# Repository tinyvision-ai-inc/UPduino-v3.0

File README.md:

# UPduino-v3.0 and 3.1

Image credit: Gregory Benjamin

## UPDuino v3.1: PCB Design Files, Designs, Documentation

The UPDuino v3.1 is a small, low cost FPGA board. The board features an on-board FPGA programmer, flash and LED with _all_ FPGA pins brought out to easy to use 0.1" header pins for fast prototyping.

The tinyVision.ai UPduino v3.x Board Features:

* Lattice UltraPlus ICE40UP5K FPGA with 5.3K LUTs, 1Mb SPRAM, 120Kb DPRAM, 8 Multipliers
* FTDI FT232H USB to SPI Device
* _ALL_ 32 FPGA GPIO on 0.1” headers
* 4MB SPI Flash
* RGB LED
* On board 3.3V and 1.2V Regulators, can supply 3.3V to your project
* Open source schematic and layout using KiCAD design tools
* Integrated into the open source [APIO toolchain](https://github.com/FPGAwars/apio)
* Works with [IceStudio](https://github.com/FPGAwars/icestudio)<sup>[nightly/dev branch only at the moment](https://downloads.icestudio.io/)</sup>

Please see the [wiki page](https://github.com/tinyvision-ai-inc/UPduino-v3.0/wiki) for the changes that were implemented from v2.1. Some salient features are:
* 4 layer board with a solid ground plane, proper layout/decoupling for good signal integrity and FPGA operation
* Access to on-board 12MHz oscillator using a jumper
* _All_ FPGA pins including LED driver pins are brought to 0.1" headers
* qSPI Flash capable
* tinyFPGA bootloader compatible 

Here are some resources for you:
* [Documentation](https://upduino.readthedocs.io/) (beyond what's on this GitHub)
* [Discord channel](https://discord.gg/3qbXujE)
* [Schematic](./Board/v3.0/UPduino_v3.0.pdf)
* [AssemblyDrawing](./Board/v3.0/UPduino_v3.0Assembly.html)
* [Blinking LED](./RTL/blink_led)
 
TinyVision.ai blog posts:
* [Magic Smoke and PTC's](https://blogs.tinyvision.ai/upduino/power/ptc/2021/12/31/magic-smoke-and-PTCs.html)
* [Lattice Modelsim on Windows](https://blogs.tinyvision.ai/modelsim/windows/linux/radiant/lattice/2022/01/01/Using-Lattice-Modelsim-on-Win-Linux.html)
* [Ground trampolines and Phase Locked Loops](https://tinyvision.ai/blogs/processing-at-the-edge/ground-trampolines-and-phase-locked-loops)

You can buy this board here:
US and non-EU orders: . 

EU Orders with VAT paid: 

For expedited shipping options, please visit the storefront at www.tinyvision.ai or email us directly at: sales at tinyvision dot ai.

## Useful links
* [Digi-Key Intro to FPGA Video series](https://youtube.com/playlist?list=PLEBQazB0HUyT1WmMONxRZn9NmQ_9CIKhb)
* [osresearch](https://github.com/osresearch/up5k): large collection of very useful code and a good overview.
* [UPduino FPGA tutorial using APIO](https://blog.idorobots.org/entries/upduino-fpga-tutorial.html)
* [A very detailed blog on implementing a RISCV in the FPGA](https://pingu98.wordpress.com/2019/04/08/)
* [Lattice iCECube2 tutorial](https://hsel.co.uk/2018/05/21/lattice-ice40-ultra-plus-fpga-gnarly-grey-upduino-tutorial-1-the-basics/)
* [Open FPGA verilog Tutorial](https://github.com/Obijuan/open-fpga-verilog-tutorial/wiki)

## The next generation of Upduino (coming soon)
* [pico-ice](https://github.com/tinyvision-ai-inc/pico-ice)

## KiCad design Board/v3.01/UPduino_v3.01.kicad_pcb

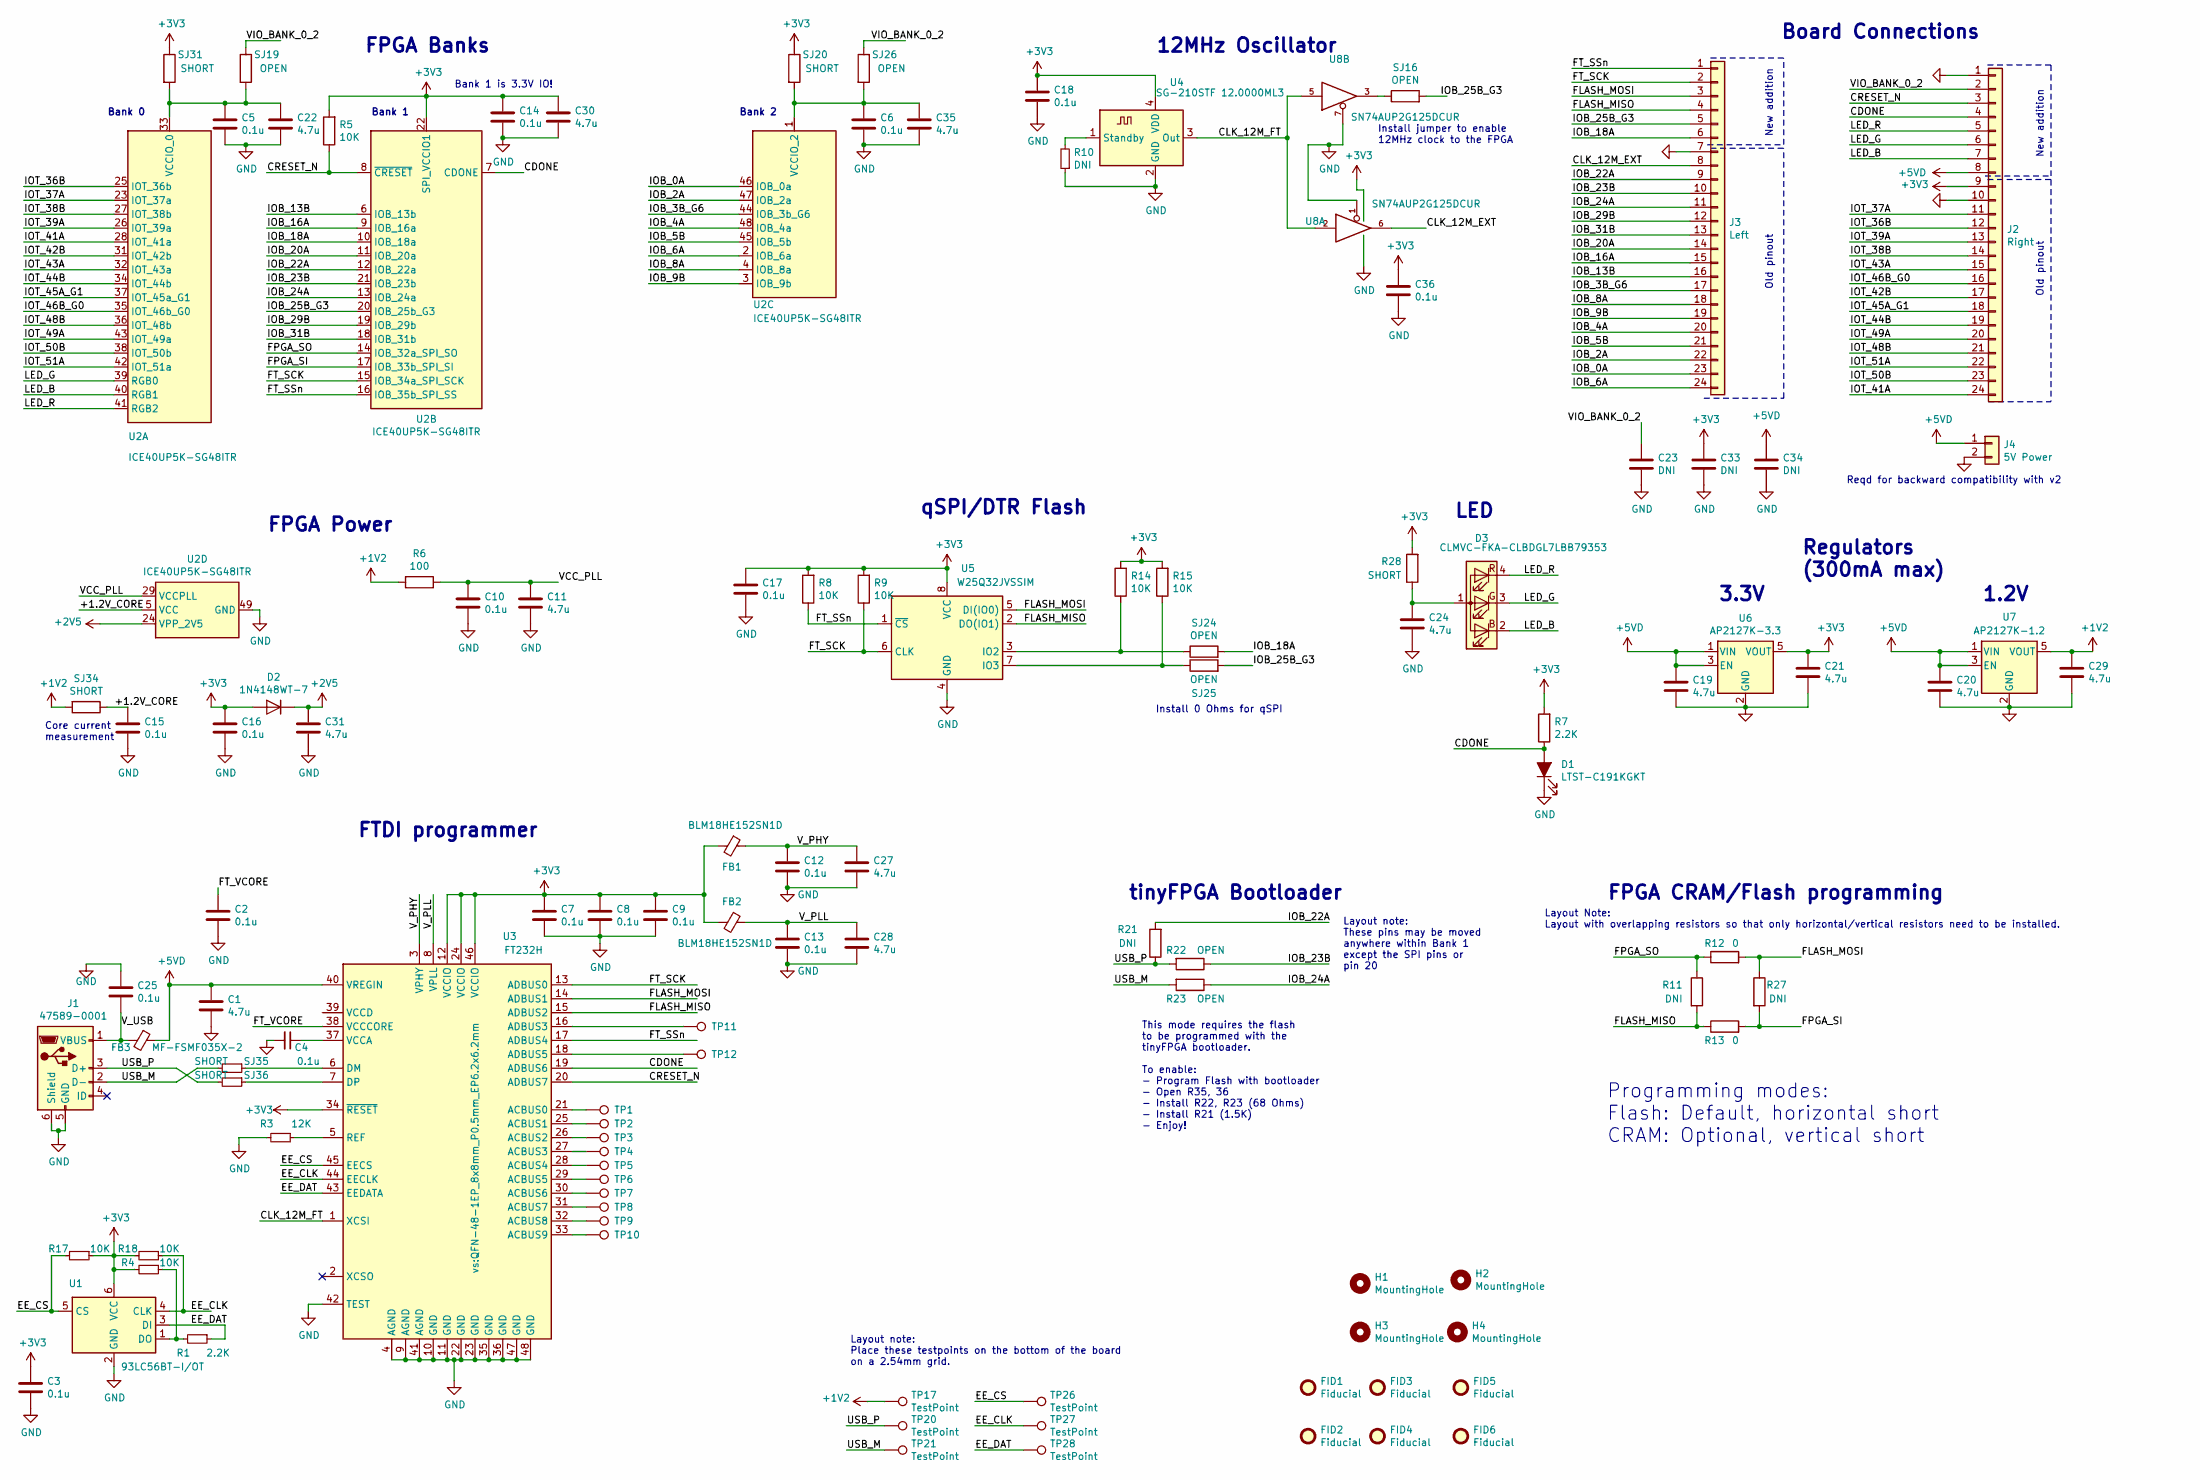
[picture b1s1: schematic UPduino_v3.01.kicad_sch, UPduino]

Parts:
C1, C11, C19, C20, C21, C22, C24, C27, C28, C29, C30, C31, C35: 4.7u; C_0603_1608Metric
C2, C3, C4, C6, C7, C8, C9, C10, C12, C13, C14, C15, C16, C17, C18, C25, C36: 0.1u; C_0603_1608Metric
C5: 0.1u; C_0603_1608Metric; MPN C1005X5R0J104K050BA
C23, C33, C34: DNI; C_0603_1608Metric
D1: LTST-C191KGKT; LED_0603_1608Metric
D2: 1N4148WT-7; D_SOD-523
D3: CLMVC-FKA-CLBDGL7LBB79353; LED_Cree-PLCC4_2x2mm_CW
FB1, FB2: BLM18HE152SN1D; L_0603_1608Metric
FB3: MF-FSMF035X-2; L_0603_1608Metric
FID1, FID2, FID3, FID4, FID5, FID6: Fiducial; Fiducial_0.75mm_Mask1.5mm
H1, H2, H3, H4: MountingHole; MountingHole_2.5mm_M3
J1: 47589-0001; USB_Micro_AB_Female_0475890001
J2: Right; PinHeader_1x24_P2.54mm_Vertical
J3: Left; PinHeader_1x24_P2.54mm_Vertical
J4: 5V Power; PinHeader_1x02_P2.54mm_Vertical
R1, R7: 2.2K; R_0603_1608Metric
R3: 12K; R_0603_1608Metric
R4, R5, R8, R9, R14, R15, R17, R18: 10K; R_0603_1608Metric
R6: 100; R_0603_1608Metric
R10, R11, R21, R27: DNI; R_0603_1608Metric
R12, R13: 0; R_0603_1608Metric
R22, R23: OPEN; SolderJumper-2_0603_Open_TrianglePad1.0x1.5mm
R28: SHORT; ShortedJumper-2_P1.3mm_Bridged_Pad1.0x1.0mm
SJ16, SJ19, SJ24, SJ25, SJ26: OPEN; SolderJumper-2_0603_Open_TrianglePad1.0x1.5mm
SJ20, SJ31, SJ34, SJ35, SJ36: SHORT; ShortedJumper-2_P1.3mm_Bridged_Pad1.0x1.0mm
TP1, TP2, TP3, TP4, TP5, TP6, TP7, TP8, TP9, TP10, TP11, TP12, TP17, TP20, TP21, TP26, TP27, TP28: TestPoint; TestPoint_Pad_D1.0mm
U1: 93LC56BT-I/OT; SOT-23-6
U2: ICE40UP5K-SG48ITR; QFN-48-1EP_7x7mm_P0.5mm_EP5.6x5.6mm
U3: FT232H; QFN-48-1EP_8x8mm_P0.5mm_EP6.2x6.2mm
U4: SG-210STF 12.0000ML3; Oscillator_SMD_Abracon_ASDMB-4Pin_2.5x2.0mm
U5: W25Q32JVSSIM; SOIC-8_5.23x5.23mm_P1.27mm
U6: AP2127K-3.3; SOT-23-5
U7: AP2127K-1.2; SOT-23-5
U8: SN74AUP2G125DCUR; VSSOP-8_2.3x2mm_P0.5mm

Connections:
+1V2: C29.1, R6.2, SJ34.2, TP17.1, U7.5 (VOUT)
+2V5: C31.1, D2.1 (K), U2.24 (VPP_2V5)
+3V3: C3.1, C7.1, C8.1, C9.1, C14.1, C16.1, C17.1, C18.1, C21.1, C30.1, C33.1, C36.1, D2.2 (A), FB1.2, FB2.2, J2.9, R4.2, R5.2, R7.2, R8.2, R9.2, R14.2, R15.2, R17.1, R18.2, R28.2, SJ20.1, SJ31.1, U1.6 (VCC), U2.22 (SPI_VCCIO1), U3.12 (VCCIO), U3.24 (VCCIO), U3.34 (~RESET), U3.46 (VCCIO), U4.4 (VDD), U5.8 (VCC), U6.5 (VOUT), U8.8 (VCC)
+5VD: C1.1, C19.1, C20.1, C34.1, FB3.1, J2.8, J4.1, U3.40 (VREGIN), U6.1 (VIN), U6.3 (EN), U7.1 (VIN), U7.3 (EN)
/+1.2V_CORE: C15.1, SJ34.1, U2.5 (VCC), U2.30 (VCC)
/CDONE: D1.2 (A), J2.4, R7.1, U2.7 (CDONE), U3.19 (ADBUS6)
/CLK_12M_EXT: J3.8, U8.6
/CLK_12M_FT: U3.1 (XCSI), U4.3 (Out), U8.2, U8.5
/CRESET_N: J2.3, R5.1, U2.8 (~CRESET), U3.20 (ADBUS7)
/EE_CLK: R18.1, TP27.1, U1.4 (CLK), U3.44 (EECLK)
/EE_CS: R17.2, TP26.1, U1.5 (CS), U3.45 (EECS)
/EE_DAT: R1.1, TP28.1, U1.3 (DI), U3.43 (EEDATA)
/FLASH_MISO: J3.4, R11.2, R13.1, U3.15 (ADBUS2), U5.2 (DO(IO1))
/FLASH_MOSI: J3.3, R12.2, R27.1, U3.14 (ADBUS1), U5.5 (DI(IO0))
/FPGA_SI: R13.2, R27.2, U2.17 (IOB_33b_SPI_SI)
/FPGA_SO: R11.1, R12.1, U2.14 (IOB_32a_SPI_SO)
/FT_SCK: J3.2, R9.1, U2.15 (IOB_34a_SPI_SCK), U3.13 (ADBUS0), U5.6 (CLK)
/FT_SSn: J3.1, R8.1, U2.16 (IOB_35b_SPI_SS), U3.17 (ADBUS4), U5.1 (~CS)
/FT_VCORE: C2.1, U3.38 (VCCCORE)
/IOB_0A: J3.23, U2.46 (IOB_0a)
/IOB_2A: J3.22, U2.47 (IOB_2a)
/IOB_3B_G6: J3.17, U2.44 (IOB_3b_G6)
/IOB_4A: J3.20, U2.48 (IOB_4a)
/IOB_5B: J3.21, U2.45 (IOB_5b)
/IOB_6A: J3.24, U2.2 (IOB_6a)
/IOB_8A: J3.18, U2.4 (IOB_8a)
/IOB_9B: J3.19, U2.3 (IOB_9b)
/IOB_13B: J3.16, U2.6 (IOB_13b)
/IOB_16A: J3.15, U2.9 (IOB_16a)
/IOB_18A: J3.6, SJ24.2, U2.10 (IOB_18a)
/IOB_20A: J3.14, U2.11 (IOB_20a)
/IOB_22A: J3.9, R21.2, U2.12 (IOB_22a)
/IOB_23B: J3.10, R22.1, U2.21 (IOB_23b)
/IOB_24A: J3.11, R23.1, U2.13 (IOB_24a)
/IOB_25B_G3: J3.5, SJ16.2, SJ25.2, U2.20 (IOB_25b_G3)
/IOB_29B: J3.12, U2.19 (IOB_29b)
/IOB_31B: J3.13, U2.18 (IOB_31b)
/IOT_36B: J2.12, U2.25 (IOT_36b)
/IOT_37A: J2.11, U2.23 (IOT_37a)
/IOT_38B: J2.14, U2.27 (IOT_38b)
/IOT_39A: J2.13, U2.26 (IOT_39a)
/IOT_41A: J2.24, U2.28 (IOT_41a)
/IOT_42B: J2.17, U2.31 (IOT_42b)
/IOT_43A: J2.15, U2.32 (IOT_43a)
/IOT_44B: J2.19, U2.34 (IOT_44b)
/IOT_45A_G1: J2.18, U2.37 (IOT_45a_G1)
/IOT_46B_G0: J2.16, U2.35 (IOT_46b_G0)
/IOT_48B: J2.21, U2.36 (IOT_48b)
/IOT_49A: J2.20, U2.43 (IOT_49a)
/IOT_50B: J2.23, U2.38 (IOT_50b)
/IOT_51A: J2.22, U2.42 (IOT_51a)
/LED_B: D3.2 (RK), J2.7, U2.40 (RGB1)
/LED_G: D3.3 (GK), J2.6, U2.39 (RGB0)
/LED_R: D3.4 (BK), J2.5, U2.41 (RGB2)
/USB_M: J1.2 (D-), R23.2, SJ35.2, TP21.1
/USB_P: J1.3 (D+), R21.1, R22.2, SJ36.2, TP20.1
/VCC_PLL: C10.1, C11.1, R6.1, U2.29 (VCCPLL)
/VIO_BANK_0_2: C23.1, J2.2, SJ19.1, SJ26.1
/V_PHY: C12.1, C27.1, FB1.1, U3.3 (VPHY)
/V_PLL: C13.1, C28.1, FB2.1, U3.8 (VPLL)
/V_USB: C25.2, FB3.2, J1.1 (VBUS)
GND: C1.2, C2.2, C3.2, C4.2, C5.2, C6.2, C7.2, C8.2, C9.2, C10.2, C11.2, C12.2, C13.2, C14.2, C15.2, C16.2, C17.2, C18.2, C19.2, C20.2, C21.2, C22.2, C23.2, C24.2, C25.1, C27.2, C28.2, C29.2, C30.2, C31.2, C33.2, C34.2, C35.2, C36.2, D1.1 (K), J1.5 (GND), J1.6 (Shield), J2.1, J2.10, J3.7, J4.2, R3.2, R10.1, U1.2 (GND), U2.49 (GND), U3.4 (AGND), U3.9 (AGND), U3.10 (GND), U3.11 (GND), U3.22 (GND), U3.23 (GND), U3.35 (GND), U3.36 (GND), U3.41 (AGND), U3.42 (TEST), U3.47 (GND), U3.48 (GND), U4.2 (GND), U5.4 (GND), U6.2 (GND), U7.2 (GND), U8.1, U8.4 (GND), U8.7
unnamed: C4.1, U3.37 (VCCA)
unnamed: C5.1, C22.1, SJ19.2, SJ31.2, U2.33 (VCCIO_0)
unnamed: C24.1, D3.1 (A), R28.1
unnamed: C6.1, C35.1, SJ20.2, SJ26.2, U2.1 (VCCIO_2)
unnamed: R1.2, R4.1, U1.1 (DO)
unnamed: R3.1, U3.5 (REF)
unnamed: R10.2, U4.1 (Standby)
unnamed: R14.1, SJ24.1, U5.3 (IO2)
unnamed: R15.1, SJ25.1, U5.7 (IO3)
unnamed: SJ16.1, U8.3
unnamed: SJ35.1, U3.6 (DM)
unnamed: SJ36.1, U3.7 (DP)
unnamed: TP1.1, U3.21 (ACBUS0)
unnamed: TP2.1, U3.25 (ACBUS1)
unnamed: TP3.1, U3.26 (ACBUS2)
unnamed: TP4.1, U3.27 (ACBUS3)
unnamed: TP5.1, U3.28 (ACBUS4)
unnamed: TP6.1, U3.29 (ACBUS5)
unnamed: TP7.1, U3.30 (ACBUS6)
unnamed: TP8.1, U3.31 (ACBUS7)
unnamed: TP9.1, U3.32 (ACBUS8)
unnamed: TP10.1, U3.33 (ACBUS9)
unnamed: TP11.1, U3.16 (ADBUS3)
unnamed: TP12.1, U3.18 (ADBUS5)

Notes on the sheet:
FPGA Banks
FPGA Power
Install jumper to enable 12MHz clock to the FPGA
Layout note: Place these testpoints on the bottom of the board on a 2.54mm grid.
New addition
Layout Note: Layout with overlapping resistors so that only horizontal/vertical resistors need to be installed.
Programming modes: Flash: Default, horizontal short CRAM: Optional, vertical short
Board Connections
Bank 2
Reqd for backward compatibility with v2
Old pinout
Layout note: These pins may be moved anywhere within Bank 1 except the SPI pins or pin 20
tinyFPGA Bootloader
Core current measurement
Install 0 Ohms for qSPI
1.2V
Bank 1
LED
qSPI/DTR Flash
FTDI programmer
3.3V
FPGA CRAM/Flash programming
This mode requires the flash to be programmed with the tinyFPGA bootloader. To enable: - Program Flash with bootloader - Open R35, 36 - Install R22, R23 (68 Ohms) - Install R21 (1.5K) - Enjoy!
Regulators (300mA max)
12MHz Oscillator
Bank 0
Bank 1 is 3.3V IO!

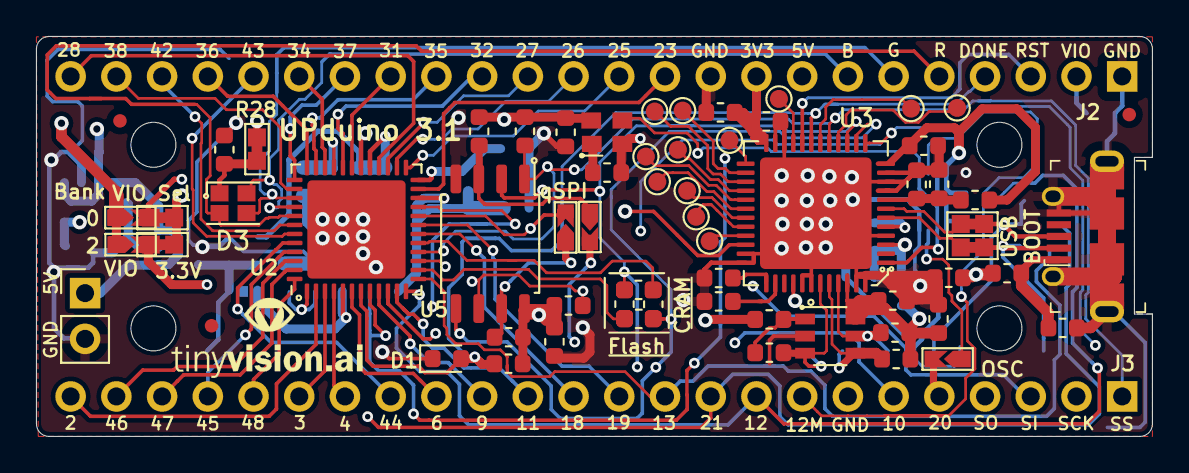
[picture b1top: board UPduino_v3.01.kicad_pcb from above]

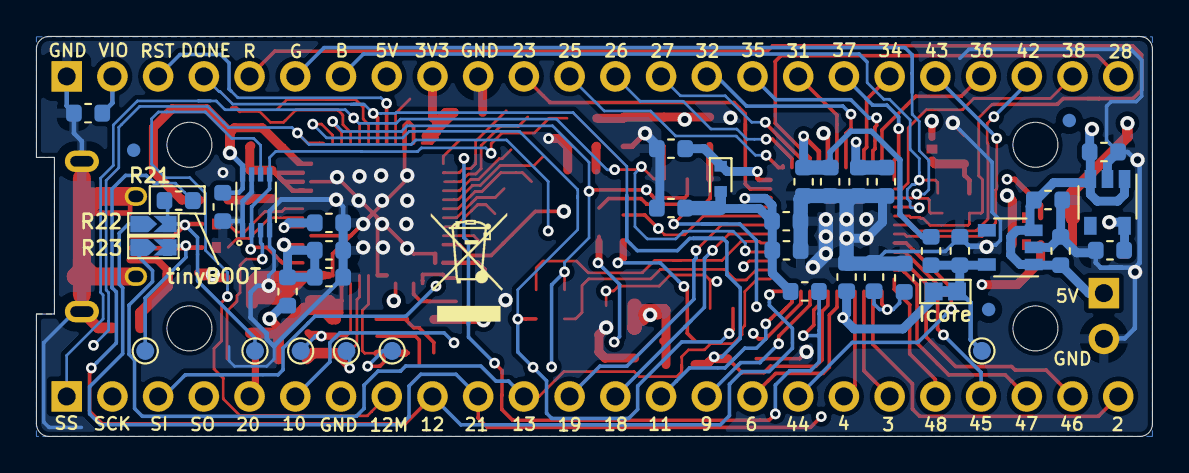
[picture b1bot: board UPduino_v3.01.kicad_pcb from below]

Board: 4 copper layers, 62.0 x 22.2 mm, 111 parts (41 on the bottom side), 86 nets.

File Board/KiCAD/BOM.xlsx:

Ref | Qnty | Value | Cmp name | Footprint | Description | Vendor
C1, C11, C21, C24, C28, C27, C19, C29, C20, C31, C30, C22, C35, | 13 | 4.7u | C | Capacitor_SMD:C_0603_1608Metric | Unpolarized capacitor
C5, C14, C6, C18, C7, C8, C9, C4, C2, C17, C10, C12, C13, C16, C15, C25, C3, C3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 | 19 | 0.1u | C | Capacitor_SMD:C_0603_1608Metric | Unpolarized capacitor
C23, C33, C34, | 3 | DNI | C | Capacitor_SMD:C_0603_1608Metric | Unpolarized capacitor
C26, | 1 | 10n | C_Small | Capacitor_SMD:C_0603_1608Metric | Unpolarized capacitor, small symbol
D1, | 1 | HSMG-C120 | LED_ALT | LED_SMD:LED_0603_1608Metric | Light emitting diode, filled shape
D2, | 1 | 1N4148W | 1N4148W | Diode_SMD:D_SOD-123 | 75V 0.15A Fast Switching Diode, SOD-123
D3, | 1 | MHPA1515RGBDT-S | LED_ARGB | vs:LED_1.65X1.55 | RGB LED, anode/red/green/blue
FB1, FB2, FB3, | 3 | BLM18HE152SN1D | Ferrite_Bead_Small | Inductor_SMD:L_0603_1608Metric | Ferrite bead, small symbol
FID1, FID3, FID5, FID2, FID4, FID6, | 6 | Fiducial | Fiducial-Mechanical-UPduino-rescue | Fiducial:Fiducial_0.75mm_Mask1.5mm
H2, H3, H4, H1, | 4 | MountingHole | MountingHole | vs:MountingHole_2.5mm_M3 | Mounting Hole without connection
J1, | 1 | 47589-0001 | USB_B_Micro | vs:USB_Micro_AB_Female_0475890001 | USB Micro Type B connector
J2, | 1 | Right | Conn_01x24 | vs:PinHeader_1x24_P2.54mm_Vertical | Generic connector, single row, 01x24, script generated (kicad-library-utils/sch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
J3, | 1 | Left | Conn_01x24 | vs:PinHeader_1x24_P2.54mm_Vertical | Generic connector, single row, 01x24, script generated (kicad-library-utils/sch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
J4, | 1 | 5V Power | Conn_01x02 | Connector_PinHeader_2.54mm:PinHeader_1x02_P2.54mm_Vertical | Generic connector, single row, 01x02, script generated (kicad-library-utils/sch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
R1, R7, | 2 | 2.2K | R | Resistor_SMD:R_0603_1608Metric | Resistor
R2, R5, R14, R15, R9, R8, R4, R18, R17, | 9 | 10K | R_Small | Resistor_SMD:R_0603_1608Metric | Resistor, small symbol
R3, | 1 | 12K | R_Small | Resistor_SMD:R_0603_1608Metric | Resistor, small symbol
R6, | 1 | 100 | R | Resistor_SMD:R_0603_1608Metric | Resistor
R10, R21, | 2 | DNI | R | Resistor_SMD:R_0603_1608Metric | Resistor
R22, R23, R24, R25, R34, R35, R36, R27, R20, R26, R19, R31, R16, | 13 | JUMPER | R | vs:SolderJumper-2_0603_Open_TrianglePad1.0x1.5mm | Resistor
RN1, | 1 | YC124-JR-071KL | R_Pack04 | Resistor_SMD:R_Array_Concave_4x0402 | 4 resistor network, parallel topology, DIP package
S1, | 1 | TC7MPB9327FK(EL) | TC7MPB9327FK(EL) | Package_SON:WSON-14-1EP_4.0x4.0mm_P0.5mm_EP2.6x2.6mm | Dual SPDT Supply Bus Switch
TP1, TP11, TP12, TP2, TP3, TP4, TP5, TP6, TP7, TP8, TP9, TP10, TP26, TP27, TP28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 | 18 | TestPoint | TestPoint | TestPoint:TestPoint_Pad_D1.0mm | test point
U1, | 1 | 93LC56BT-I/OT | 93LCxxBxxOT-Memory_EEPROM-UPduino-rescue | vs:SOT-23-6
U2, | 1 | ICE40UP5K-SG48ITR | ICE40UP5K-SG48ITR-FPGA_Lattice | Package_DFN_QFN:QFN-48-1EP_7x7mm_P0.5mm_EP5.6x5.6mm
U3, | 1 | FT232H | FT232H | vs:QFN-48-1EP_8x8mm_P0.5mm_EP6.2x6.2mm | FT232Hx, Hi Speed Single Channel USB UART/FIFO, LQFP/QFN-48
U4, | 1 | SG-210STF 12.0000ML3 | ASDMB-xxxMHz-Oscillator-UPduino-rescue | Oscillator:Oscillator_SMD_Abracon_ASDMB-4Pin_2.5x2.0mm
U5, | 1 | W25Q32JVSSIM | W25Q32JVSS-Memory_Flash-UPduino-rescue | Package_SO:SOIC-8_5.23x5.23mm_P1.27mm
U6, | 1 | AP2127K-3.3 | AP2127K-3.3 | Package_TO_SOT_SMD:SOT-23-5 | 300mA low dropout linear regulator, shutdown pin, 2.5V-6V input voltage, 3.3V f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
U7, | 1 | AP2127K-1.2 | AP2127K-1.2 | Package_TO_SOT_SMD:SOT-23-5 | 300mA low dropout linear regulator, shutdown pin, 2.5V-6V input voltage, 1.2V f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
U8, | 1 | SN74AUP2G125DCUR | 74AUC2G125 | Package_SO:VSSOP-8_2.3x2mm_P0.5mm | Dual Buffer Tri-State, Low-Voltage CMOS

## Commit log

2019-11-18 Initial version of schematic
    Thanks to Raffi for all the input!
2019-11-18 Updated PDF with the design
2019-11-18 Updated with missing symbols
2019-11-19 Updated with input from Lattice
    - Changed diode dropper to create 2.5V to 1N4148, added decoupling cap after that
    - Added 5V header
    - Added zero ohm jumper to measure core power consumption
    - No cascading of LDO's
    - Added 1.8V regulator and output to the board pins
2019-11-19 Minor edits
    - Added jumpers to USB_P/M to allow the tinyFPGA programmer to work
    - Minor text changes
2019-11-20 More changes!
    Programming scheme finalized
    Schematic cleanup
2019-12-03 Updated with latest schematics and layout
2019-12-09 Updated schematic
2019-12-23 Final CAD
2019-12-24 Fixed MISO/MOSI bug
    PDF schematic update only! Rest of the design will be updated soon.
2019-12-26 Fixed mosi/miso bug, added silkscreen changes
2020-03-17 Final version
2020-03-17 Post merge cleanup
2020-03-17 Added bringup, various bits of documentation and also the blinky and PDC files.
2020-03-20 Update UPduino_v3.0.kicad_pcb
    Fixed duplicate silkscreen (pin 35->36) on IOT48B connection
2020-03-25 Cleaned up silkscreen, created new gerbers
2020-03-26 Fixed lost library references. Edited schematic file by hand to resolve horrible name mangling
2020-04-12 Added v2 to address changes from v1
2020-04-12 Changed diode footprint, LED, modified FTDI reset, silkscreen for board and a few other changes
2020-05-11 Fixed silkscreen, removed CRAM/Flash programming switch
2020-05-12 Added BoM to the zipfile
2020-05-12 Added BoM
2020-05-12 Cleanup
2020-05-26 Added fab drawing
2020-05-26 Added fab drawings
2020-06-04 Added bringup document
2020-06-04 Minor edits to clean up PDC and FPGA build flow
2020-06-06 Fixed RGB LED bug
2020-06-08 Added board images
2020-06-08 Fixed links
2020-06-08 Fixed assembly drawing link
2020-06-08 Removed CE logo, added RoHS logo, regenerated gerbers.
2020-06-09 Fixed pass/fail criteria for 3.3V and LED
2020-07-06 Test Webhook Integration
2020-07-06 Upload Favicon
2020-07-06 Upload Fonts
2020-07-06 Updated gerbers and fab files
2020-07-07 Bugfix for 12MHz clock pin
    @ggrummer identified a bug that the 12MHz clock and ground pins are swapped.
2020-07-07 Regenerated gerbers
2020-07-07 Removed reference to C26 in schematic notes for tinyFPGA bootloader mode
    Thanks to @ggrummer
2020-07-09 Added country of origin USA on back silkscreen
2020-07-11 Fixed DRC by assigning FTDI pad to ground which it wasnt for some reason!
2020-07-27 Modified silkscreen and updated gerbers. Used for final production run
2020-08-06 Initial set of planned tutorials
2020-08-06 Added PMOD usage
2020-08-06 Added PMOD and bank programming
2020-08-06 3 color LED disconnect docs
2020-08-06 Added CRAM/Flash programming options
2020-08-06 Added oscillator section
2020-08-06 Added qSPI mode docs
2020-08-06 Changed R and B ports in schematic symbol for the 3 color LED, thanks to Pablo Cossutta
2020-08-07 Added clarification of LED orientation on the fab drawing
2020-08-08 Fix a typo in README.md
2020-08-11 Changed schematic to reflect shorted and open jumpers
2020-08-22 Added hi res picture
2020-08-22 Added image attribution
2020-08-22 Added EEPROM files
2020-09-08 Update README.md
    Added readthedocs link
2020-09-08 Added assembly file
2020-09-09 Update qspi_flash.rst
    Added notes for why qSPI isnt a default based on Chuck Pateros feedback.
2020-09-13 Changed PDC to PCF
2020-12-13 UPduino Lattice Radiant and Reveal v2.2 example project and Soft JTAG demo --- whf
2020-12-14 Minimal design with all pins for power testing
2020-12-14 Deleted temp files
2020-12-14 Moved directories
2020-12-14 Removed implementation files
2020-12-14 Fixed minor nits
2021-04-18 Added pinout
2021-04-18 Fixed pinout format
2021-04-18 Added resources
2021-04-18 Fixed syntax
2021-04-18 Fixed nits, added a few more resources
2021-04-21 Added pinout drawing
2021-04-21 Fixed spacing bug
2021-04-27 Restored to the older text drawing and fixed the pinout for the 12MHz/Ground issue
2021-04-27 Added Global clock notes
2021-04-27 Fixed list indents
2021-04-27 Fixed global clock pin allocation and added note about qSPI mode
2021-06-22 Added Errata note
2021-08-30 Removed incorrect note on gpio_10
2022-01-02 Changed pin 25 from gpio_24 to gpio_2
    Thanks to @riz
2022-04-15 typo
2022-04-21 Updates and additions
    Removed survey link as it is no longer active
    Added tutorial on using iCECube2 to program Upduino and the Digi-Key FPGA video series to Useful links section
    Corrected tiny typo "beyond whats" changed to "beyond what's) on line 31
    Added TinyVision.ai blog post sections and links to posts themselves
2022-04-22 Updated index.rst to reflect readme.md
2022-04-22 Typo
    teh to the
2022-04-23 Added tutorial link
    Tutorial series on FPGA development using icestudio/FPGA wars open source toolchain
2022-04-23 Added Tutorial
2022-04-23 Updated toolchain links
    old link was to a deprecated repo, new link is to the recommended installation method for the yosys stack
2022-04-24 Added Icestudio link
    also provided brief explanation as to the necessity of installing dev branch/nightly build of icestudio as current release doesn't have upduino 3.1 in boards list.
2022-05-14 Fix broken links
    they were internal rather than external links, so just led to 404s
2022-05-15 add an additional resource, the examples from XarkLabs
    This example has other valuable resources like guides on simulation, pullup resistors, validation, etc.
2022-05-28 Patronics Patch (#1)
    * Fix broken links
    they were internal rather than external links, so just led to 404s
    * add an additional resource, the examples from XarkLabs
    This example has other valuable resources like guides on simulation, pullup resistors, validation, etc.
    authored-by: Patrick Leiser <patrick27leiser@yahoo.com>
2022-05-29 cleaned up the language and increased readability
2022-05-29 cleaned up the language and increased readability
    Patronics Patch (#1)
    * Fix broken links
    they were internal rather than external links, so just led to 404s
    * add an additional resource, the examples from XarkLabs
    This example has other valuable resources like guides on simulation, pullup resistors, validation, etc.
    authored-by: Patrick Leiser <patrick27leiser@yahoo.com>
2022-05-29 Minor edits (#21)
    * Patronics Patch (#1)
    * Fix broken links
    they were internal rather than external links, so just led to 404s
    * add an additional resource, the examples from XarkLabs
    This example has other valuable resources like guides on simulation, pullup resistors, validation, etc.
2022-08-23 remove an autogenerated file
2023-04-26 Added link to TabbyCAD
2023-12-20 Create CNAME
2024-01-16 Update Makefile
    fixed a single spelling mistake
2024-07-06 Fixed schematic bug on EEPROM, this was only on the SCH and not in the PDF or the board.
2025-01-22 Added link to the upduino-jtag repo
2026-03-07 Fix Sphinx 7.x compatibility and improve Getting Started docs
    - Fix conf.py for current Sphinx: add_stylesheet() → add_css_file(), language = 'en'
    - Fix toctree typo: disconnect_tricolor_led → disconnect_tri_color_led
    - Rewrite first_steps.rst with clearer instructions for 2026 users:
    - Explain Micro USB data cable requirement (vs charge-only)
    - Add USB-C adapter note for modern Macs
    - Add terminal commands for macOS/Linux/Windows to verify serial port
